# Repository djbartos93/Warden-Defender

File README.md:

# Warden-Defender
###Door controller software for Warden

-----
The Warden Defender is the hardware/software implimentation for the [Warden-Manager](https://github.com/djbartos93/Warden-Manager). The basic idea behind the Warden Defender is an open source door controller for RIFD keyless entry. There will be a custom interface board to allow for easy setup just plugging in the reader and strike then connecting it to the arduino.

The system will send a request to the server to ask for access, if the card ID matches an ID in the database and the user is eabled the server will send the unlock signal and the Defender will open the door.

## TO DO:
- Basics
 - [ ] HID Prox reader interface
 - [ ] Electronic Strike interface
 - [ ] Network Interface
- Hardware
 - [X] Design custom reader/strike interface board (V1 done, ordering to test soon)
 - [ ] ~~POE Compatable somehow~~
 - [ ] Power supply possible 3rd vreg for arduino?
 - [ ] Get custom board printed for testing
- Software
 - [ ] Network connectivity to server
 - [ ] Open strike from network without swiping card
 - [ ] offline access list?
 - [ ] management web page for board?
 - [ ] setup different loops for manage/control webpage and reader 

##Best Practices for setup:

##Links to hardware:

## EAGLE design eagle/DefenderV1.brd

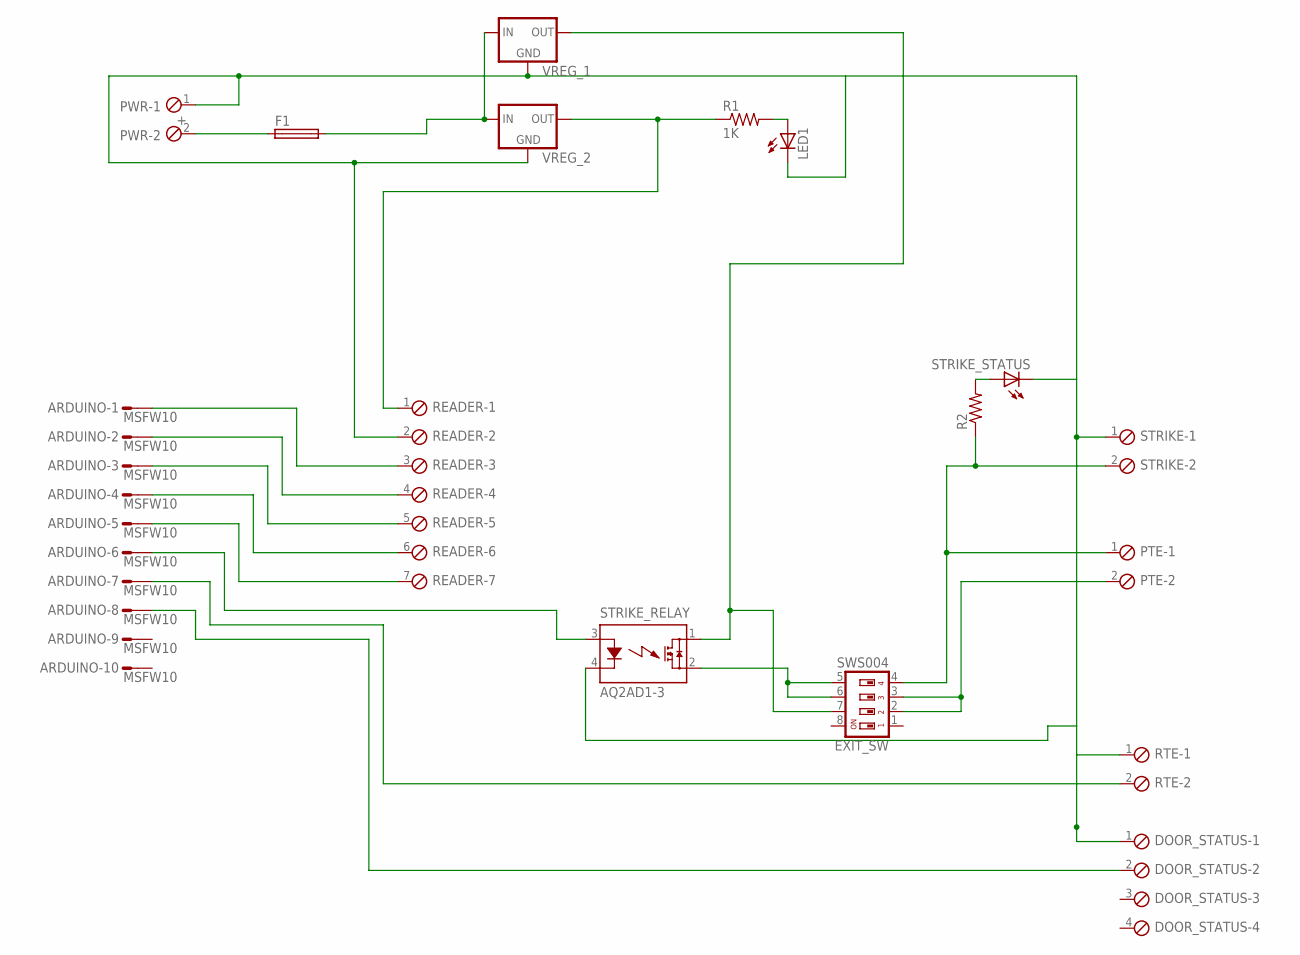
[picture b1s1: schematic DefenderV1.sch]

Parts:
ARDUINO: MSFW10
DOOR_STATUS: MPT4; 4POL254
EXIT_SW: SWS004; SMS-004
F1: GSH15
LED1: LED5MM
PTE: MPT2; 2POL254
PWR: +; 2POL254
R1: 1K; 0204/7
R2: R-US_0204/7; 0204/7
READER: MPT7; 7POL254
RTE: MPT2; 2POL254
STRIKE: MPT2; 2POL254
STRIKE_RELAY: AQ2AD1-3; AQ1
STRIKE_STATUS: LED5MM
VREG_1, VREG_2: 78XXL

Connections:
unnamed: F1.2, VREG_1.IN, VREG_2.IN
unnamed: F1.1, PWR.2
unnamed: DOOR_STATUS.1, LED1.K (C), PWR.1, READER.2, RTE.1, STRIKE.1, STRIKE_RELAY.4 (K), STRIKE_STATUS.K (C), VREG_1.GND, VREG_2.GND
unnamed: ARDUINO.1, READER.3
unnamed: ARDUINO.2, READER.4
unnamed: ARDUINO.3, READER.5
unnamed: EXIT_SW.5, EXIT_SW.6, STRIKE_RELAY.2 (DS2)
unnamed: R2.2, STRIKE_STATUS.A
unnamed: ARDUINO.4, READER.6
unnamed: EXIT_SW.4, PTE.1, R2.1, STRIKE.2
unnamed: EXIT_SW.2, EXIT_SW.3, PTE.2
unnamed: LED1.A, R1.2
unnamed: ARDUINO.5, READER.7
unnamed: ARDUINO.6, STRIKE_RELAY.3 (A)
unnamed: ARDUINO.7, RTE.2
unnamed: EXIT_SW.7, STRIKE_RELAY.1 (DS1), VREG_1.OUT
unnamed: ARDUINO.8, DOOR_STATUS.2
unnamed: R1.1, READER.1, VREG_2.OUT

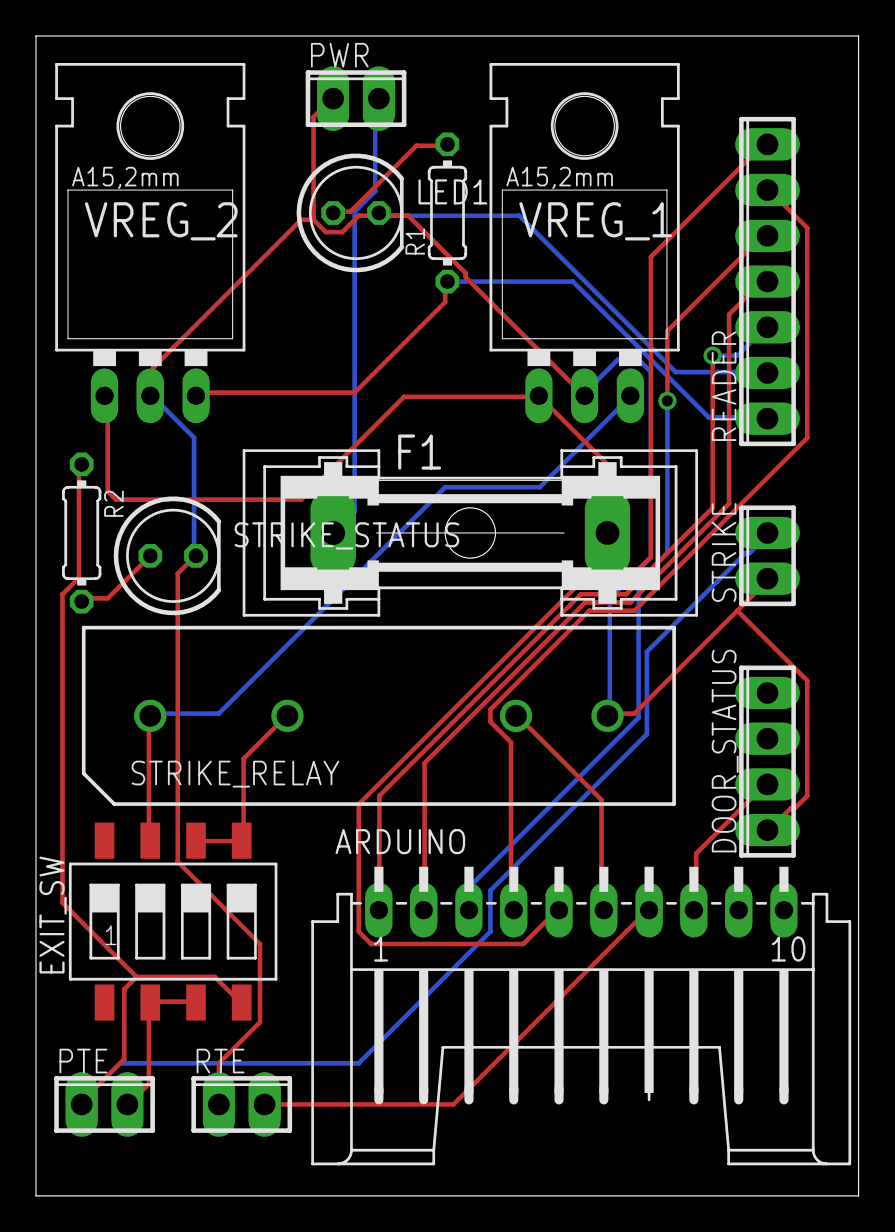
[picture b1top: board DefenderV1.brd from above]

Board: 2 copper layers, 45.7 x 64.4 mm, 16 parts (0 on the bottom side), 18 nets.

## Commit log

2015-10-16 Readme update
2015-10-16 Starting Point for defender software. Untested.
2015-10-16 some network shit
2015-10-16 updated with link to manager
2015-10-17 PCB and schematic for controller
2015-10-20 this code might work?
    no arduino yet to test with
